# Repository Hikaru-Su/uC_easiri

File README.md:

# uC_easiri
## can通信系エアシリ制御ボード
1. 電源が切り離されているため、電磁弁用の電源が必要。
3. 12V時に電磁弁に印加される電流が160mAほどだったため8個同時に動かす場合、1Aを超えるため電源を分けた。<br>

|MCUピン|エアシリ番号|
|---|---|
|pin9|es5|
|pin10|es6|
|pin11|es7|
|pin12|es8|
|pin13|es1|
|pin14|es2|
|pin15|es3|
|pin18|es4|

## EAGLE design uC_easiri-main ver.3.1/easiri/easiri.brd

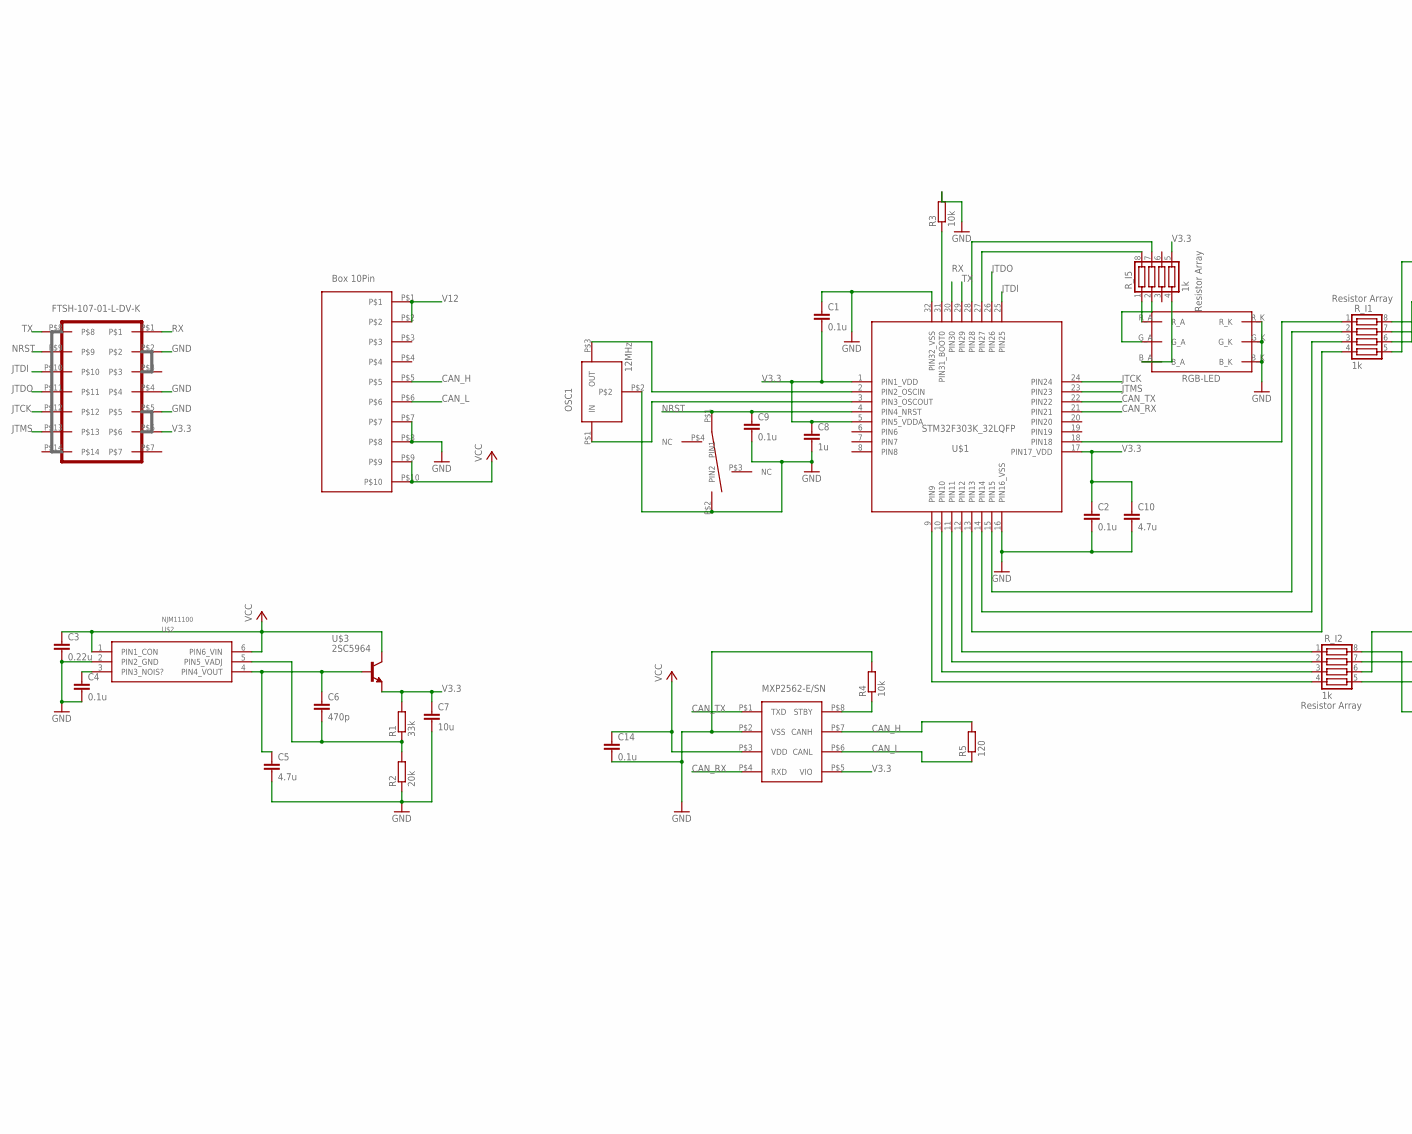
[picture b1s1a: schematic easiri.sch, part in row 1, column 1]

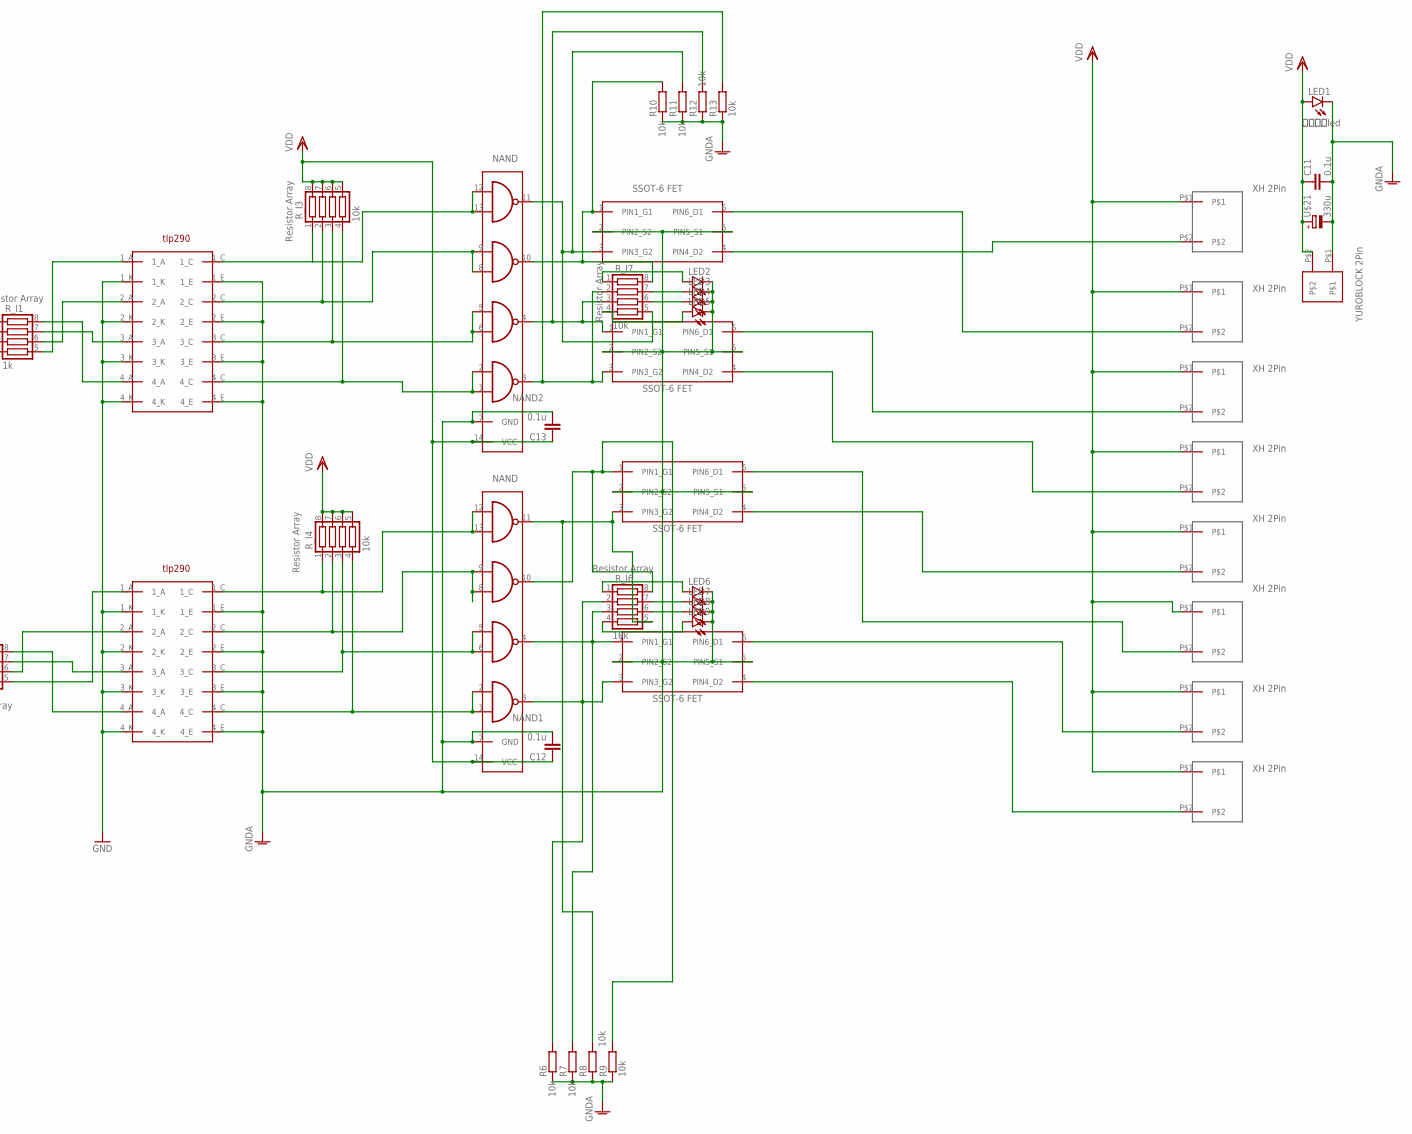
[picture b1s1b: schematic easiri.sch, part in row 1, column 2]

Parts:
BOX10P-L2: BOX10PBOX10P-L; BOX10P-L
C1, C2, C4, C9, C11, C12, C13, C14: 0.1u; C1608
C3: 0.22u; C2012
C5, C10: 4.7u; C2012
C6: 470p; C1608
C7: 10u; C2012
C8: 1u; C1608
ES1, ES2, ES3, ES4, ES5, ES6, ES7, ES8: XH_2P
LED1: 抵抗内蔵led; LED5MM
LED2, LED3, LED4, LED5, LED6, LED7, LED8, LED9: 1608LED; 1608
NAND1, NAND2: 14PIN_NAND2; TSSOP14
OSC1: 12MHz; CSTNE#
R1: 33k; 1608
R2: 20k; 1608
R3, R4, R6, R7, R8, R9, R10, R11, R12, R13: 10k; 1608
R5: 120; 1608
R_I1, R_I2, R_I5: 1k; 0603X4RESISTOR
R_I3, R_I4, R_I6, R_I7: 10k; 1005X4RESISTOR
U$1: STM32F303K_32LQFP; LQFP32-7X7
U$2: NJM11100; SOT23-6
U$3: 2SC5964; PCP
U$4: TAKUTOSUITTI2
U$5: MCP2562MCP2561-SN; SOIC8
U$6, U$7: TLP290-4; TLP290
U$8, U$9, U$10, U$11: SSOT6_FET; SSOT6
U$12: YUROBLOCK2
U$13: FTSH-107-01-L-DV-K
U$21: 330u; 1014CAPA
U$23: RGB_LED

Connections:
CAN_H: BOX10P-L2.P$5, R5.2, U$5.P$7 (CANH)
CAN_L: BOX10P-L2.P$6, R5.1, U$5.P$6 (CANL)
CAN_RX: U$1.21 (PIN21), U$5.P$4 (RXD)
CAN_TX: U$1.22 (PIN22), U$5.P$1 (TXD)
GND: BOX10P-L2.P$7, BOX10P-L2.P$8, C1.1, C2.2, C3.2, C4.2, C5.2, C7.2, C8.2, C9.2, C10.2, C14.2, OSC1.P$2, R2.1, R3.2, R4.2, U$1.16 (PIN16_VSS), U$1.32 (PIN32_VSS), U$2.2 (PIN2_GND), U$4.P$2 (PIN2), U$5.P$2 (VSS), U$6.1_K, U$6.2_K, U$6.3_K, U$6.4_K, U$7.1_K, U$7.2_K, U$7.3_K, U$7.4_K, U$13.P$2, U$13.P$4, U$13.P$5, U$23.B_K, U$23.G_K, U$23.R_K
GNDA: C11.2, C12.2, C13.2, LED1.K (C), LED2.K, LED3.K, LED4.K, LED5.K, LED6.K, LED7.K, LED8.K, LED9.K, NAND1.7 (GND), NAND2.7 (GND), R6.1, R7.1, R8.1, R9.1, R10.1, R11.1, R12.1, R13.1, U$6.1_E, U$6.2_E, U$6.3_E, U$6.4_E, U$7.1_E, U$7.2_E, U$7.3_E, U$7.4_E, U$8.2 (PIN2_S2), U$8.5 (PIN5_S1), U$9.2 (PIN2_S2), U$9.5 (PIN5_S1), U$10.2 (PIN2_S2), U$10.5 (PIN5_S1), U$11.2 (PIN2_S2), U$11.5 (PIN5_S1), U$12.P$1, U$21.-
JTCK: U$1.24 (PIN24), U$13.P$12
JTDI: U$1.25 (PIN25), U$13.P$10
JTDO: U$1.26 (PIN26), U$13.P$11
JTMS: U$1.23 (PIN23), U$13.P$13
unnamed: C6.2, R1.1, R2.2, U$2.5 (PIN5_VADJ)
unnamed: C4.1, U$2.3 (PIN3_NOIS?)
unnamed: C5.1, C6.1, U$2.4 (PIN4_VOUT), U$3.1 (B)
unnamed: OSC1.P$1 (IN), U$1.3 (PIN3_OSCOUT)
unnamed: OSC1.P$3 (OUT), U$1.2 (PIN2_OSCIN)
unnamed: R3.1, U$1.31 (PIN31_BOOT0)
unnamed: R_I1.8, U$6.4_A
unnamed: R_I1.7, U$6.3_A
unnamed: R4.1, U$5.P$8 (STBY)
unnamed: R_I1.6, U$6.2_A
unnamed: R_I5.8, U$1.27 (PIN27)
unnamed: R_I2.6, U$7.2_A
unnamed: NAND2.12 (4B), NAND2.13 (4A), R_I3.1, U$6.1_C
unnamed: R_I2.7, U$7.3_A
unnamed: R_I2.8, U$7.4_A
unnamed: R_I2.5, U$7.1_A
unnamed: NAND1.5 (2B), NAND1.6 (2A), R_I4.3, U$7.3_C
unnamed: NAND2.5 (2B), NAND2.6 (2A), R_I3.3, U$6.3_C
unnamed: NAND1.1 (1A), NAND1.2 (1B), R_I4.4, U$7.4_C
unnamed: NAND1.3 (1Y), R6.2, R_I6.2, U$11.3 (PIN3_G2)
unnamed: NAND1.8 (3A), NAND1.9 (3B), R_I4.2, U$7.2_C
unnamed: LED8.A, R_I6.6
unnamed: LED7.A, R_I6.7
unnamed: ES3.P$2, U$9.6 (PIN6_D1)
unnamed: ES1.P$2, U$8.4 (PIN4_D2)
unnamed: ES2.P$2, U$8.6 (PIN6_D1)
unnamed: ES4.P$2, U$9.4 (PIN4_D2)
unnamed: LED4.A, R_I7.6
unnamed: ES6.P$2, U$10.6 (PIN6_D1)
unnamed: ES7.P$2, U$11.6 (PIN6_D1)
unnamed: R_I2.1, U$1.12 (PIN12)
unnamed: ES8.P$2, U$11.4 (PIN4_D2)
unnamed: R_I2.2, U$1.11 (PIN11)
unnamed: R_I2.3, U$1.10 (PIN10)
unnamed: R_I2.4, U$1.9 (PIN9)
unnamed: R_I1.4, U$1.13 (PIN13)
unnamed: R_I1.3, U$1.14 (PIN14)
unnamed: R_I1.5, U$6.1_A
unnamed: R_I1.2, U$1.15 (PIN15)
unnamed: R_I5.7, U$1.28 (PIN28)
unnamed: R_I1.1, U$1.18 (PIN18)
unnamed: R_I5.4, U$23.B_A
unnamed: R_I5.1, U$23.R_A
unnamed: R_I5.2, U$23.G_A
unnamed: NAND1.4 (2Y), R7.2, R_I6.3, U$11.1 (PIN1_G1)
unnamed: ES5.P$2, U$10.4 (PIN4_D2)
unnamed: NAND2.8 (3A), NAND2.9 (3B), R_I3.2, U$6.2_C
unnamed: NAND2.1 (1A), NAND2.2 (1B), R_I3.4, U$6.4_C
unnamed: NAND1.12 (4B), NAND1.13 (4A), R_I4.1, U$7.1_C
unnamed: NAND1.10 (3Y), R9.2, R_I6.8, U$10.1 (PIN1_G1)
unnamed: NAND2.3 (1Y), R13.2, R_I7.2, U$9.3 (PIN3_G2)
unnamed: NAND2.4 (2Y), R12.2, R_I7.3, U$9.1 (PIN1_G1)
unnamed: NAND2.10 (3Y), R10.2, R_I7.8, U$8.1 (PIN1_G1)
unnamed: NAND2.11 (4Y), R11.2, R_I7.5, U$8.3 (PIN3_G2)
unnamed: LED9.A, R_I6.4
unnamed: LED6.A, R_I6.1
unnamed: NAND1.11 (4Y), R8.2, R_I6.5, U$10.3 (PIN3_G2)
unnamed: LED3.A, R_I7.7
unnamed: LED5.A, R_I7.4
unnamed: LED2.A, R_I7.1
NRST: C9.1, U$1.4 (PIN4_NRST), U$4.P$1 (PIN1), U$13.P$9
RX: U$1.30 (PIN30), U$13.P$1
TX: U$1.29 (PIN29), U$13.P$8
V3.3: C1.2, C2.1, C7.1, C8.1, C10.1, R1.2, R_I5.5, U$1.1 (PIN1_VDD), U$1.5 (PIN5_VDDA), U$1.17 (PIN17_VDD), U$3.3 (E), U$5.P$5 (VIO), U$13.P$6
V12: BOX10P-L2.P$1, BOX10P-L2.P$2
VCC: BOX10P-L2.P$9, BOX10P-L2.P$10, C3.1, C14.1, U$2.1 (PIN1_CON), U$2.6 (PIN6_VIN), U$3.2 (C), U$3.2@2 (C), U$5.P$3 (VDD)
VDD: C11.1, C12.1, C13.1, ES1.P$1, ES2.P$1, ES3.P$1, ES4.P$1, ES5.P$1, ES6.P$1, ES7.P$1, ES8.P$1, LED1.A, NAND1.14 (VCC), NAND2.14 (VCC), R_I3.5, R_I3.6, R_I3.7, R_I3.8, R_I4.5, R_I4.6, R_I4.7, R_I4.8, U$12.P$2, U$21.+

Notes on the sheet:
FTSH-107-01-L-DV-K
Box 10Pin
Resistor Array
RGB-LED
XH 2Pin
SSOT-6 FET
NAND
YUROBLOCK 2Pin
MXP2562-E/SN

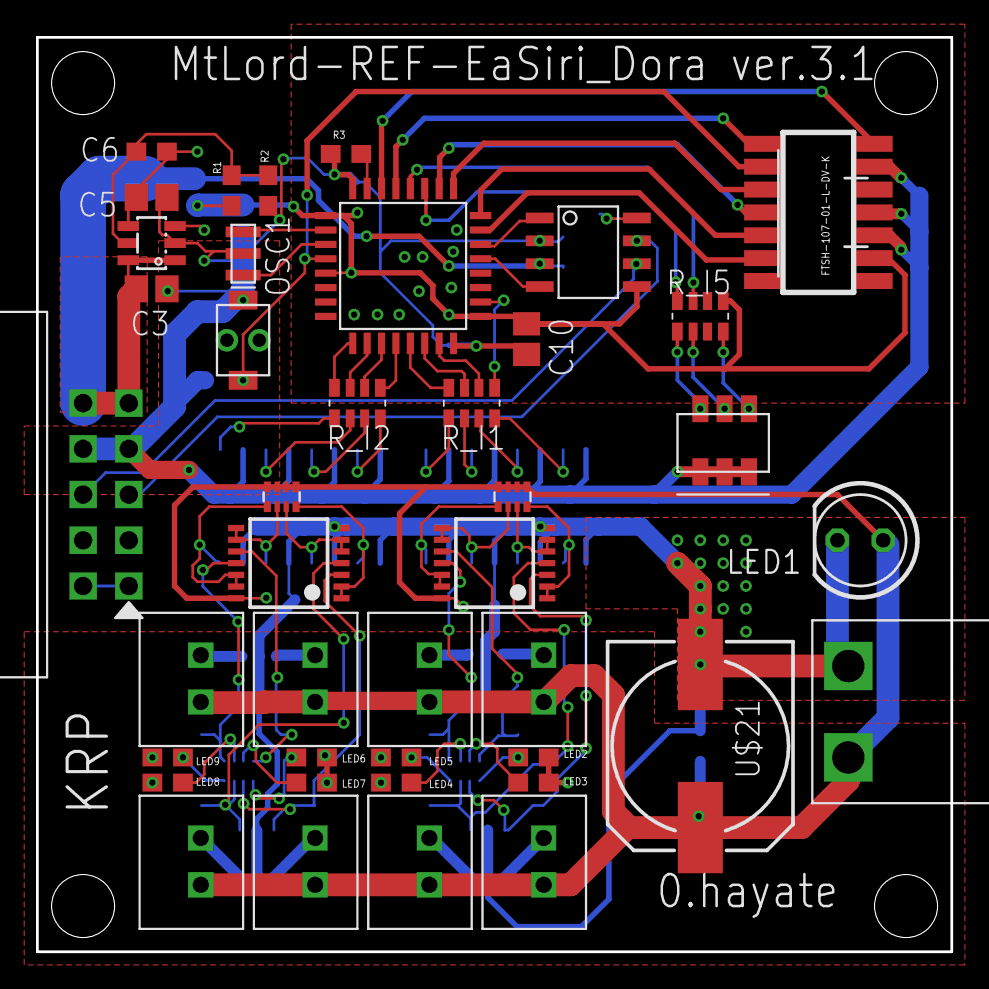
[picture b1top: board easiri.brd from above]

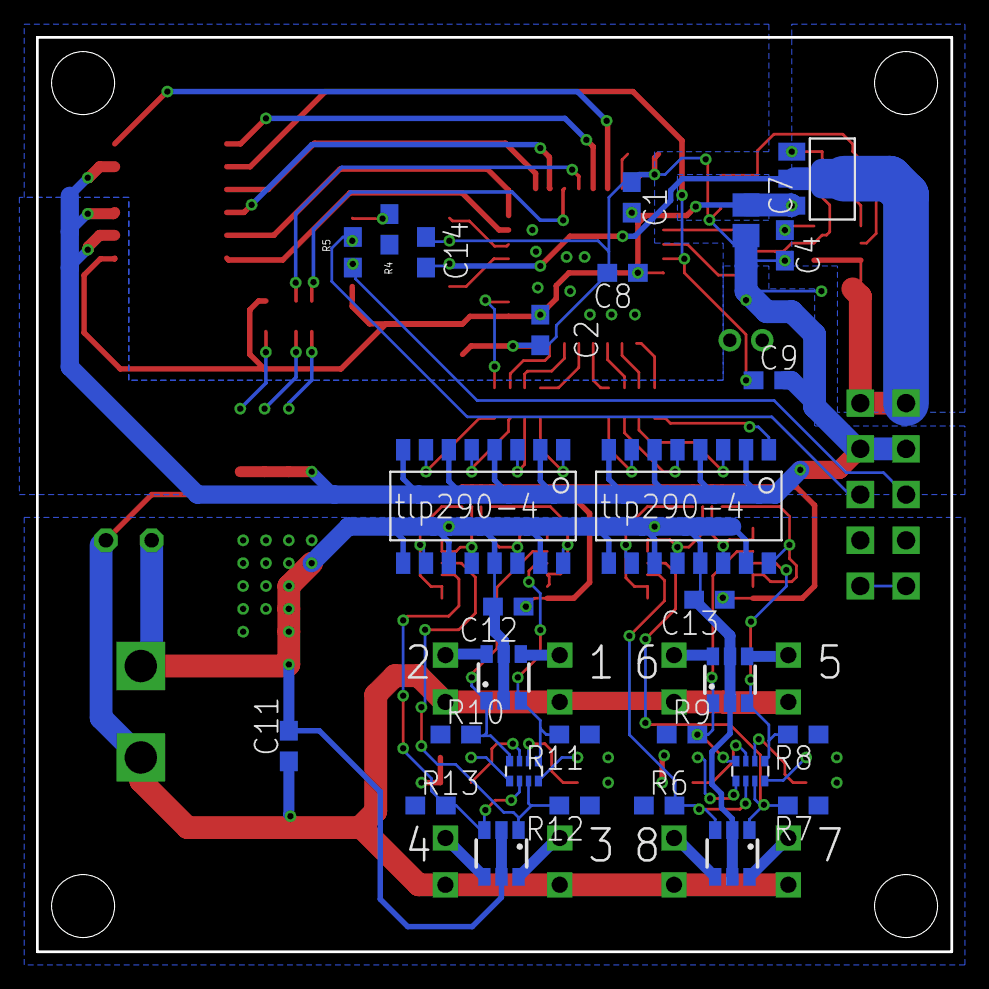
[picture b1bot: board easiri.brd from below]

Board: 2 copper layers, 50.8 x 50.8 mm, 70 parts (29 on the bottom side), 77 nets.

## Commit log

2020-10-22 エアシリンダードライバボウド
    神山先輩のエアシリンダ制御基板を参照及び改良した制御ボード
    電源が切り離されているため、電磁弁用の電源が必要。
    12V時に電磁弁に印加される電流が160mAほどだったため8個同時に動かす場合、1Aを超えるため電源を分けた。
2020-10-22 usartとかを追加
    電源確認or通信確認ようledをついか、pcでシリアルモニタによるデバッグができるようにusartを追加
2020-10-22 Add files via upload
    電源確認or通信確認ようledをついか、pcでシリアルモニタによるデバッグができるようにusartを追加
    canのピンボックスが半分の位置になかったがどうしてもいやだったので半分の位置に来るようにした
2020-10-23 ロゴの位置を直した
    自己主張大事！！
2020-10-24 canトランシーバ用のコンデンサを追加
    fet駆動にインバッタをはっさんだ。ゲートにledを入れたがそれがそのままプルダウン抵抗に置き換わるかも
2020-10-25 ゲートにプルダウン抵抗を追加
2021-11-09 mcp2562スタンバイピンプルダウン
